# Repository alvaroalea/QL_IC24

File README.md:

# SINCLAIR QL IC24 - i8049 Replacement

# THIS SCHEMATIC DO NOT WORK
## NOT FOR USE, THIS IS ONLY A MOCKUP, WORK IN PROGRESS

(C) 2022 Alvaro Alea Fernandez.

This work is licensed under a Creative Commons Attribution-NonCommercial-ShareAlike 4.0 International License.

http://creativecommons.org/licenses/by-nc-sa/4.0/

This board will replace the second processor of the Sinclair QL, sometimes know as "Hermes"

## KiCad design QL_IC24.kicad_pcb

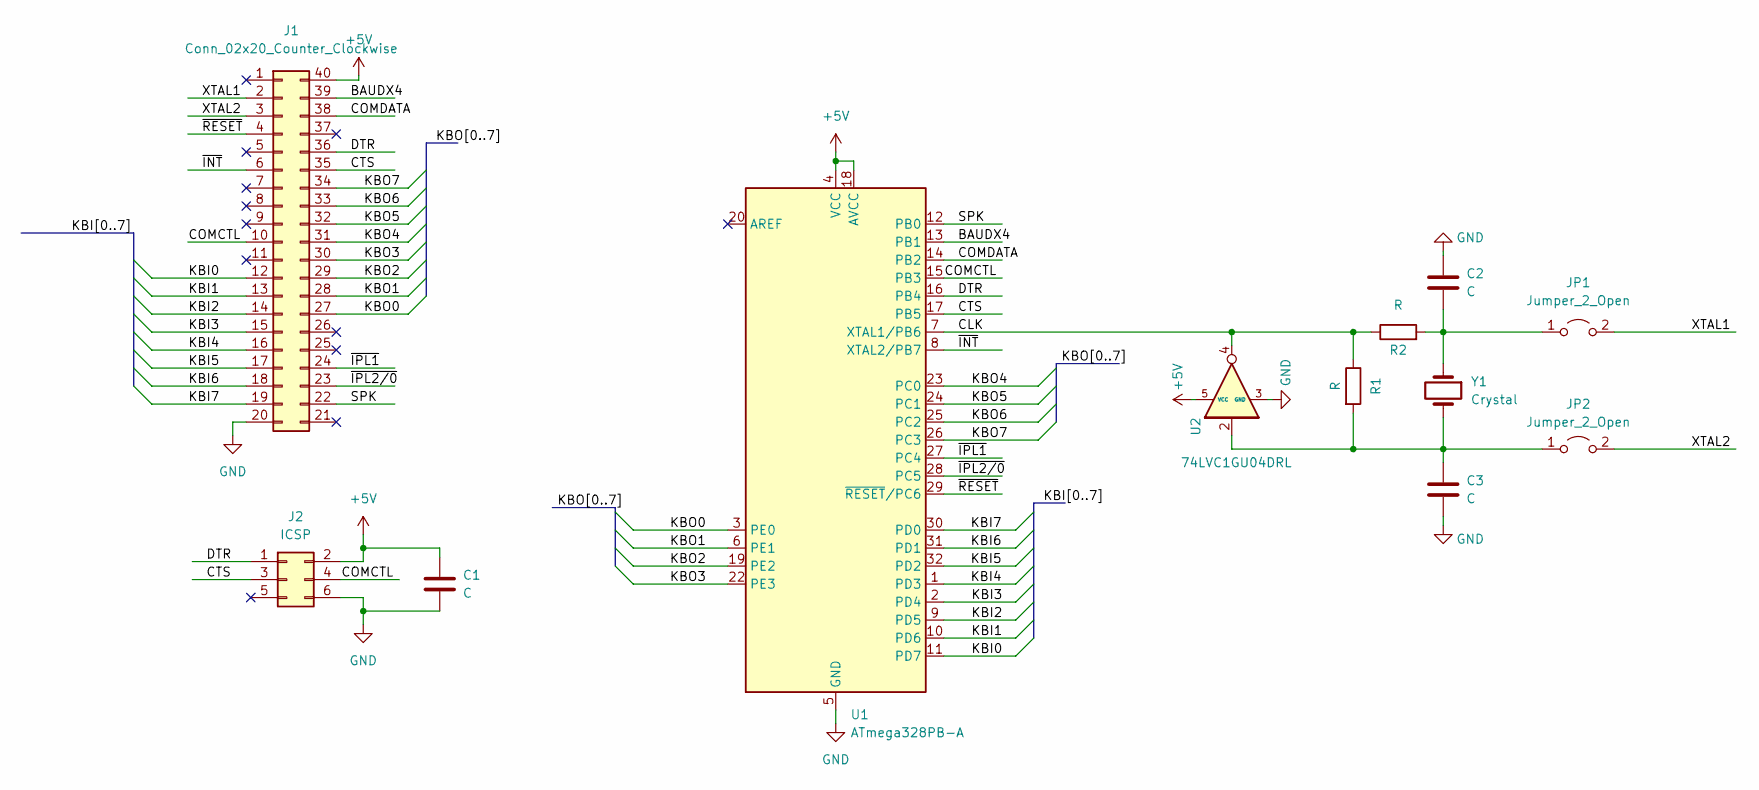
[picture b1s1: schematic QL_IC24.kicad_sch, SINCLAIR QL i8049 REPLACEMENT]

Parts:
C1, C2, C3: C; C_0603_1608Metric_Pad1.08x0.95mm_HandSolder
J1: Conn_02x20_Counter_Clockwise; DIP-40_W15.24mm_Socket
J2: ICSP; PinHeader_2x03_P2.54mm_Vertical
JP1, JP2: Jumper_2_Open; SolderJumper-2_P1.3mm_Open_Pad1.0x1.5mm
R1, R2: R; R_0603_1608Metric_Pad0.98x0.95mm_HandSolder
U1: ATmega328PB-A; TQFP-32_7x7mm_P0.8mm
U2: 74LVC1GU04DRL; SOT-23-5_HandSoldering
Y1: Crystal; Crystal_SMD_HC49-SD

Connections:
+5V: C1.1, J1.40, J2.2, U1.4 (VCC), U1.18 (AVCC), U2.5 (VCC)
/BAUDX4: J1.39, U1.13 (PB1)
/CLK: R1.1, R2.1, U1.7 (XTAL1/PB6), U2.4
/COMCTL: J1.10, J2.4, U1.15 (PB3)
/COMDATA: J1.38, U1.14 (PB2)
/CTS: J1.35, J2.3, U1.17 (PB5)
/DTR: J1.36, J2.1, U1.16 (PB4)
/KBI0: J1.12, U1.11 (PD7)
/KBI1: J1.13, U1.10 (PD6)
/KBI2: J1.14, U1.9 (PD5)
/KBI3: J1.15, U1.2 (PD4)
/KBI4: J1.16, U1.1 (PD3)
/KBI5: J1.17, U1.32 (PD2)
/KBI6: J1.18, U1.31 (PD1)
/KBI7: J1.19, U1.30 (PD0)
/KBO0: J1.27, U1.3 (PE0)
/KBO1: J1.28, U1.6 (PE1)
/KBO2: J1.29, U1.19 (PE2)
/KBO3: J1.30, U1.22 (PE3)
/KBO4: J1.31, U1.23 (PC0)
/KBO5: J1.32, U1.24 (PC1)
/KBO6: J1.33, U1.25 (PC2)
/KBO7: J1.34, U1.26 (PC3)
/SPK: J1.22, U1.12 (PB0)
/XTAL1: J1.2, JP1.2 (B)
/XTAL2: J1.3, JP2.2 (B)
/~INT: J1.6, U1.8 (XTAL2/PB7)
/~IPL1: J1.24, U1.27 (PC4)
/~IPL2/0: J1.23, U1.28 (PC5)
/~RESET: J1.4, U1.29 (~RESET/PC6)
GND: C1.2, C2.2, C3.2, J1.20, J2.6, U1.5 (GND), U1.21 (GND), U2.3 (GND)
unnamed: C2.1, JP1.1 (A), R2.2, Y1.1
unnamed: C3.1, JP2.1 (A), R1.2, U2.2, Y1.2

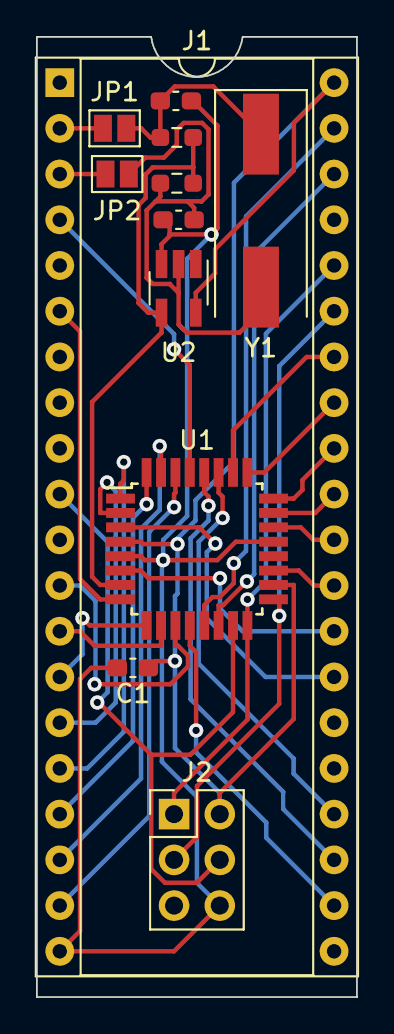
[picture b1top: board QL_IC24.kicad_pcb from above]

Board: 2 copper layers, 17.8 x 53.3 mm, 12 parts (0 on the bottom side), 33 nets.

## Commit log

2022-02-13 Initial
2022-02-13 update (C)

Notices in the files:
QL_IC24.kicad_pcb:
(C) 2022 Alvaro Alea Fdz.
README.md:
CC BY-NC-SA 4.0
